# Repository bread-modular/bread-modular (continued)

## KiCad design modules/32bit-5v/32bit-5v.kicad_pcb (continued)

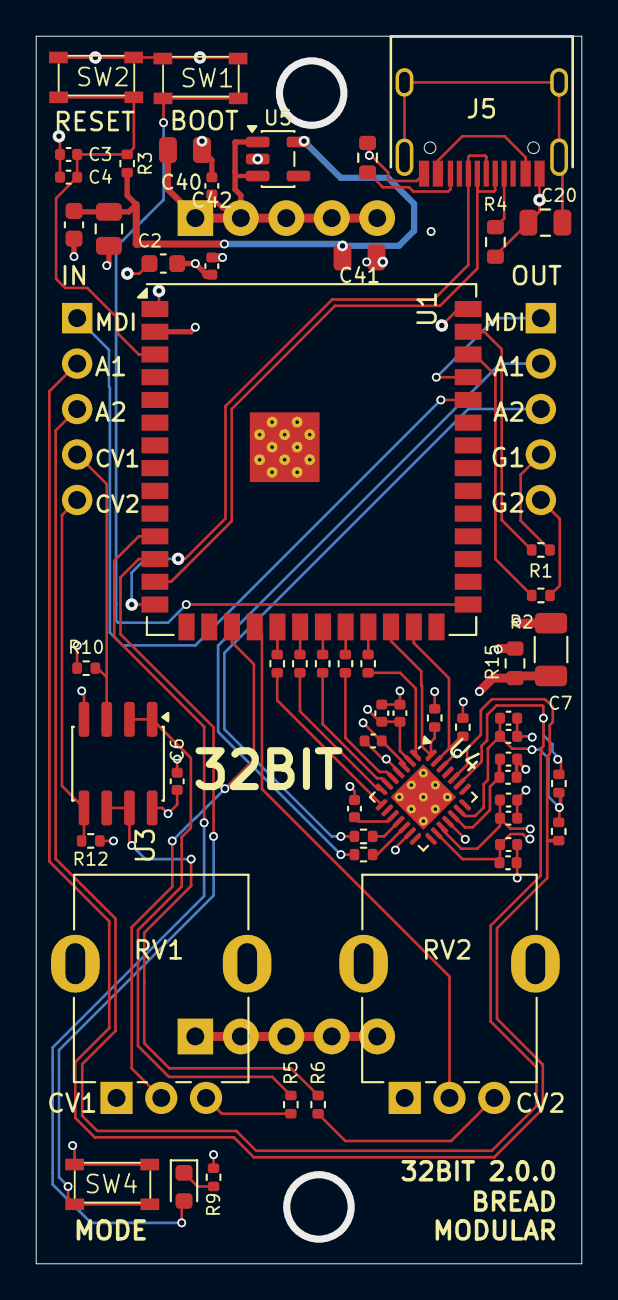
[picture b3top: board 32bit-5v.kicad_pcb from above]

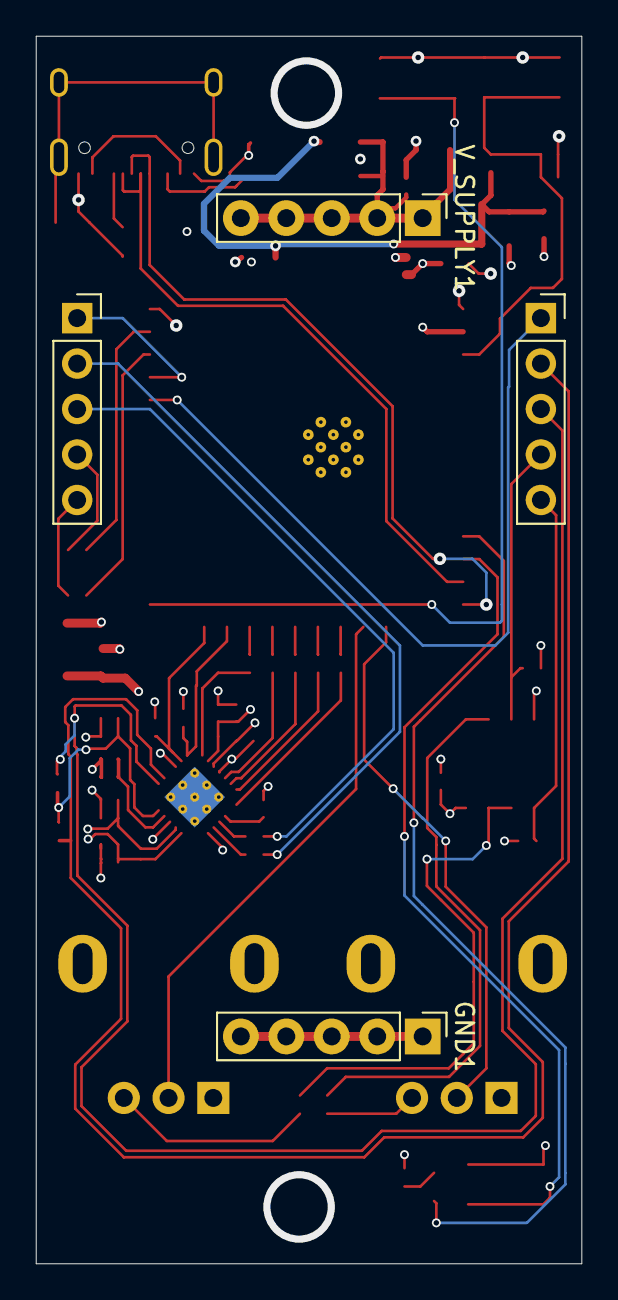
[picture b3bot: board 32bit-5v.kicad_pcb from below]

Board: 4 copper layers, 30.5 x 68.6 mm, 61 parts (4 on the bottom side), 51 nets.

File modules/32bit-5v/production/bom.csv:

Designator,Footprint,Quantity,Value,LCSC Part #
"C1,C4,C6,C21,C22,C26,C34,C36,C39",0402,9,0.1uf,
"C2,C8",0603,2,10uf,
C3,0402,1,1uf,
"C5,C27,C33,C35,C37,C38",0402,6,10uf,
"C7,C9,C10,C11,C12,C13",1206,6,100uf,
C20,0805,1,10nf,
C40,0805,1,10uf,C15850
C41,0805,1,22uf,C45783
D1,LED_0603_1608Metric,1,LED,
FB1,0805,1,GZ2012D121TF,
"GND1,V_SUPPLY1",Power_Connector,2,Conn_01x05_Pin,
"INPUT1,OUTPUT1",PinSocket_1x05_P2.54mm_Vertical,2,Conn_01x05_Socket,
J5,HRO-TYPE-C-31-M-12,1,USB_C_Receptacle_USB2.0_14P,
"R1,R2,R9,R13,R17",0402,5,1k,
R3,0402,1,10k,
"R4,R11",0603,2,5.1k,
"R5,R6",0402,2,1.5k,
"R7,R8,R14,R18,R26",0402,5,33,
"R10,R12,R16,R19",0402,4,100k,
R15,0603,1,10,
"R24,R25",0402,2,4.7k,
"RV1,RV2",Potentiometer_RV09,2,50k,
"SW1,SW2,SW4",K2-1808SN-A4SW-01,3,K2-1808SN-A4SW-01,
U1,ESP32-S3-WROOM-1U,1,ESP32-S3-WROOM-1U-N16R8,
U3,SOIC-8-1EP_3.9x4.9mm_P1.27mm_EP2.29x3mm,1,MCP6002-xSN,
U4,QFN-28-1EP_4x4mm_P0.45mm_EP2.4x2.4mm_ThermalVias,1,~,
U5,SOT-223-3_TabPin2,1,AP7361C-33E-13,C500795

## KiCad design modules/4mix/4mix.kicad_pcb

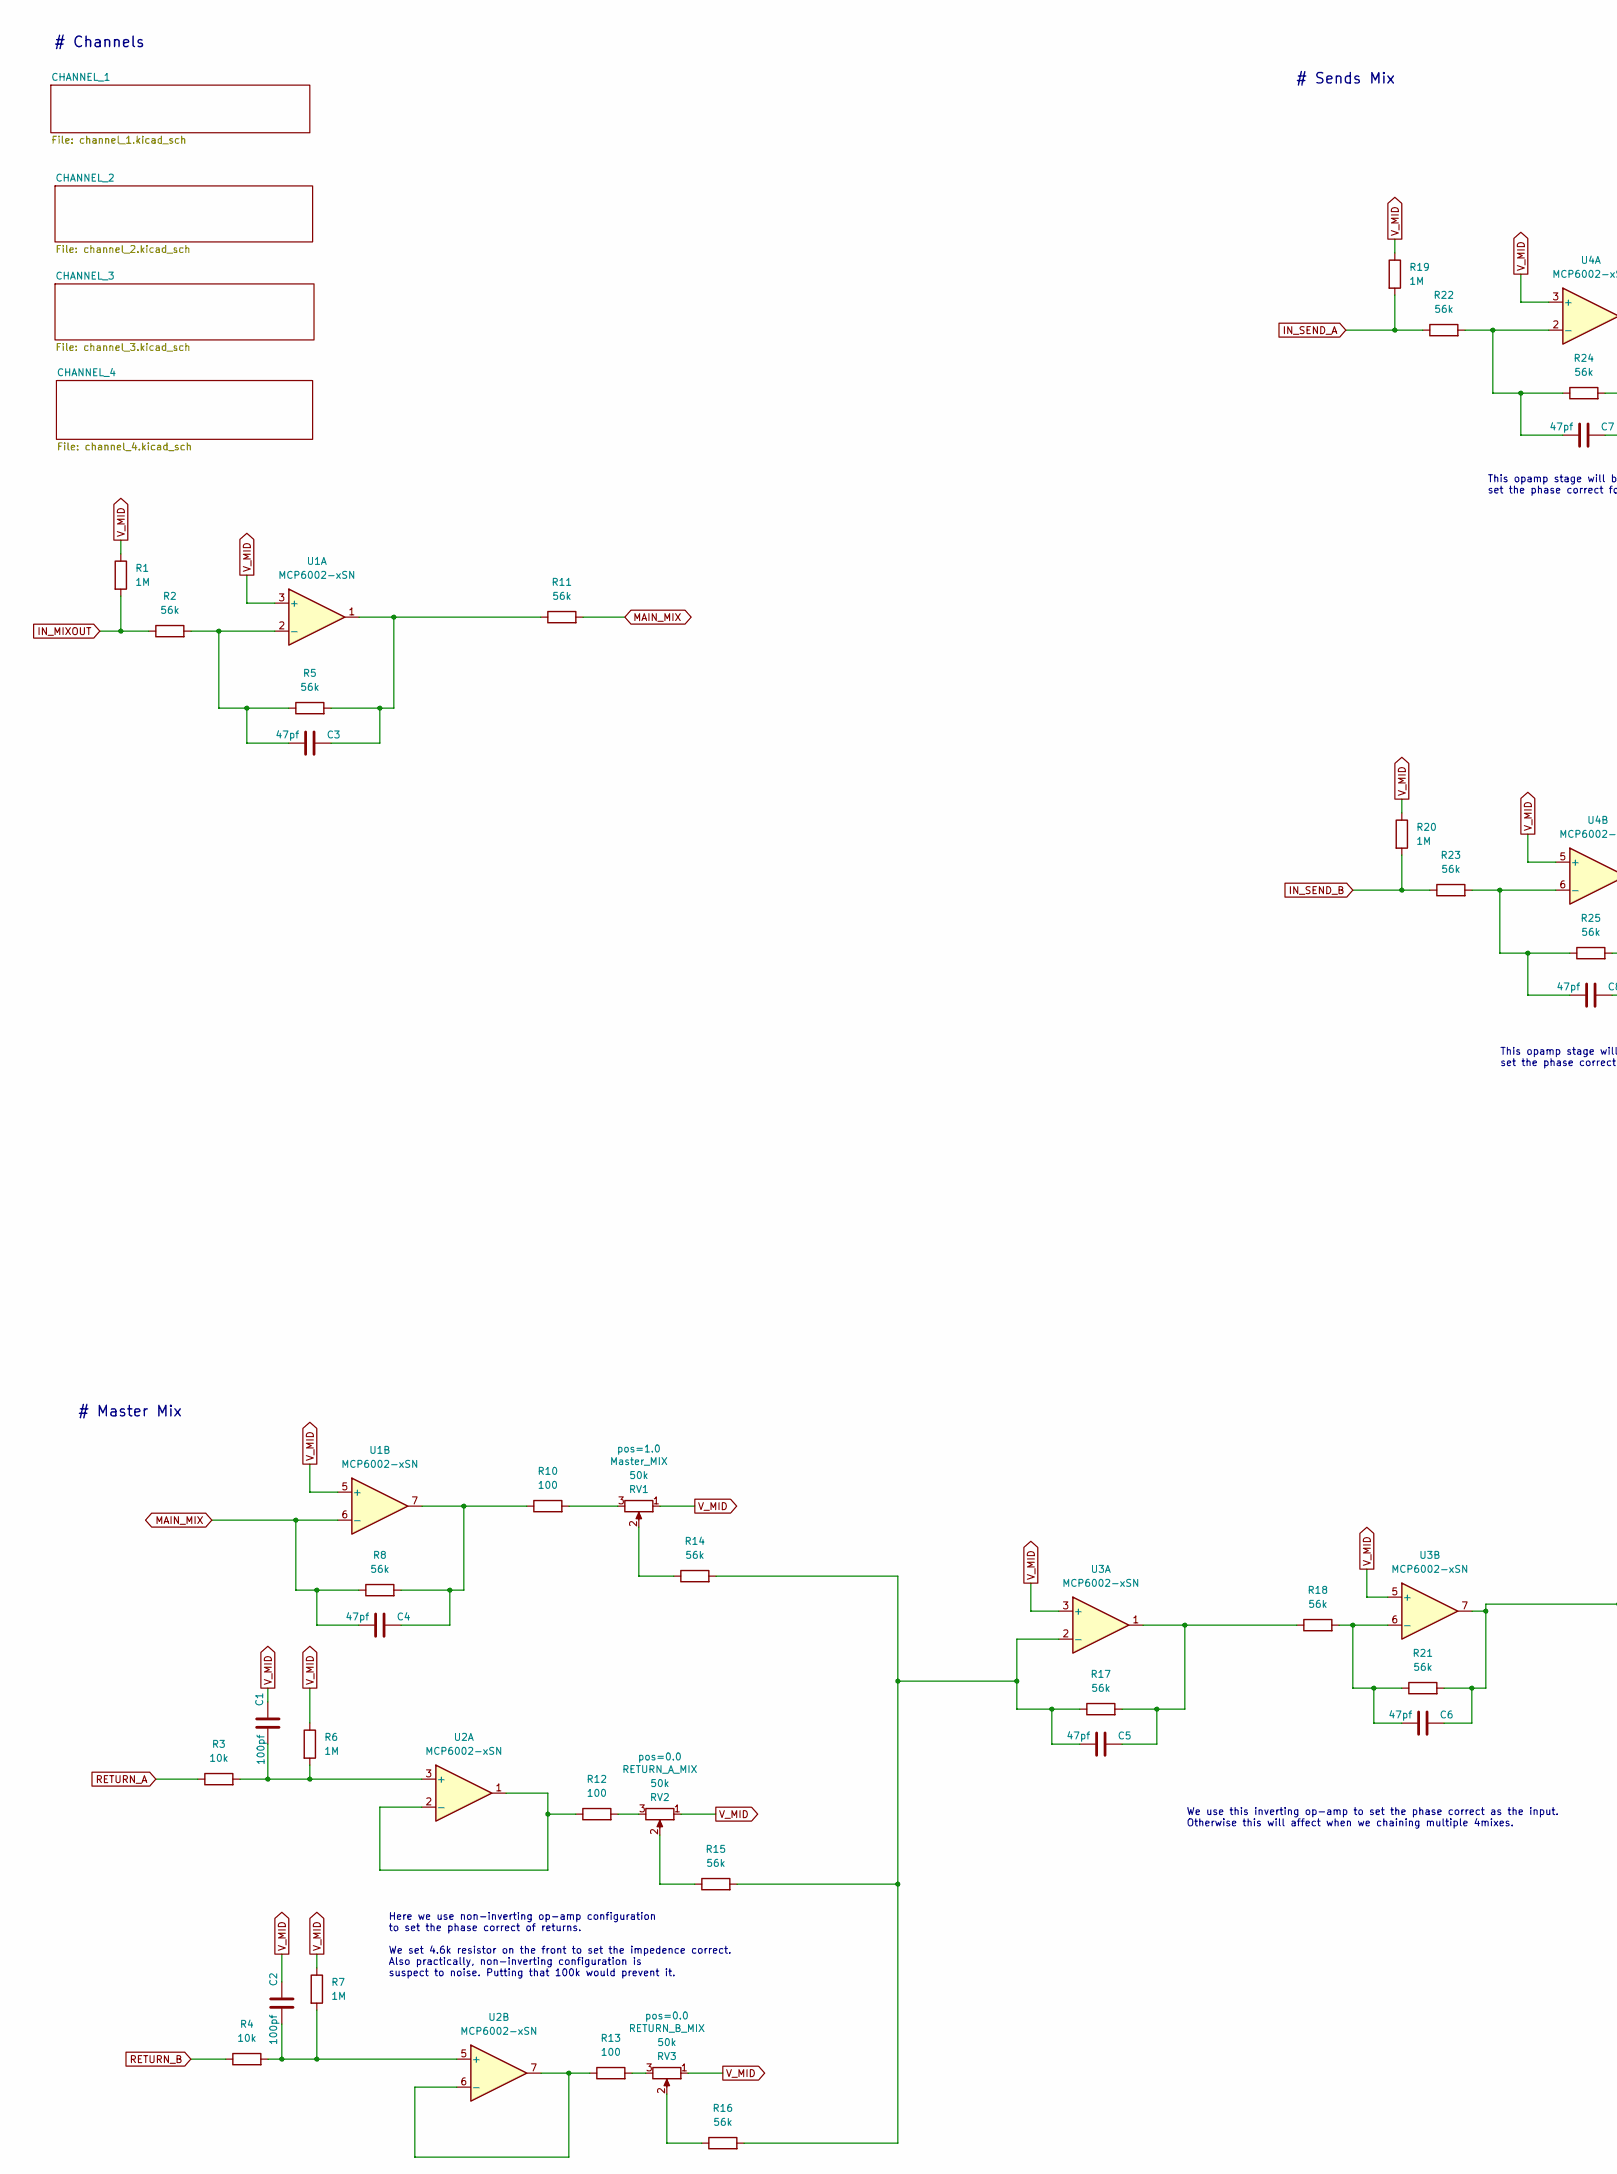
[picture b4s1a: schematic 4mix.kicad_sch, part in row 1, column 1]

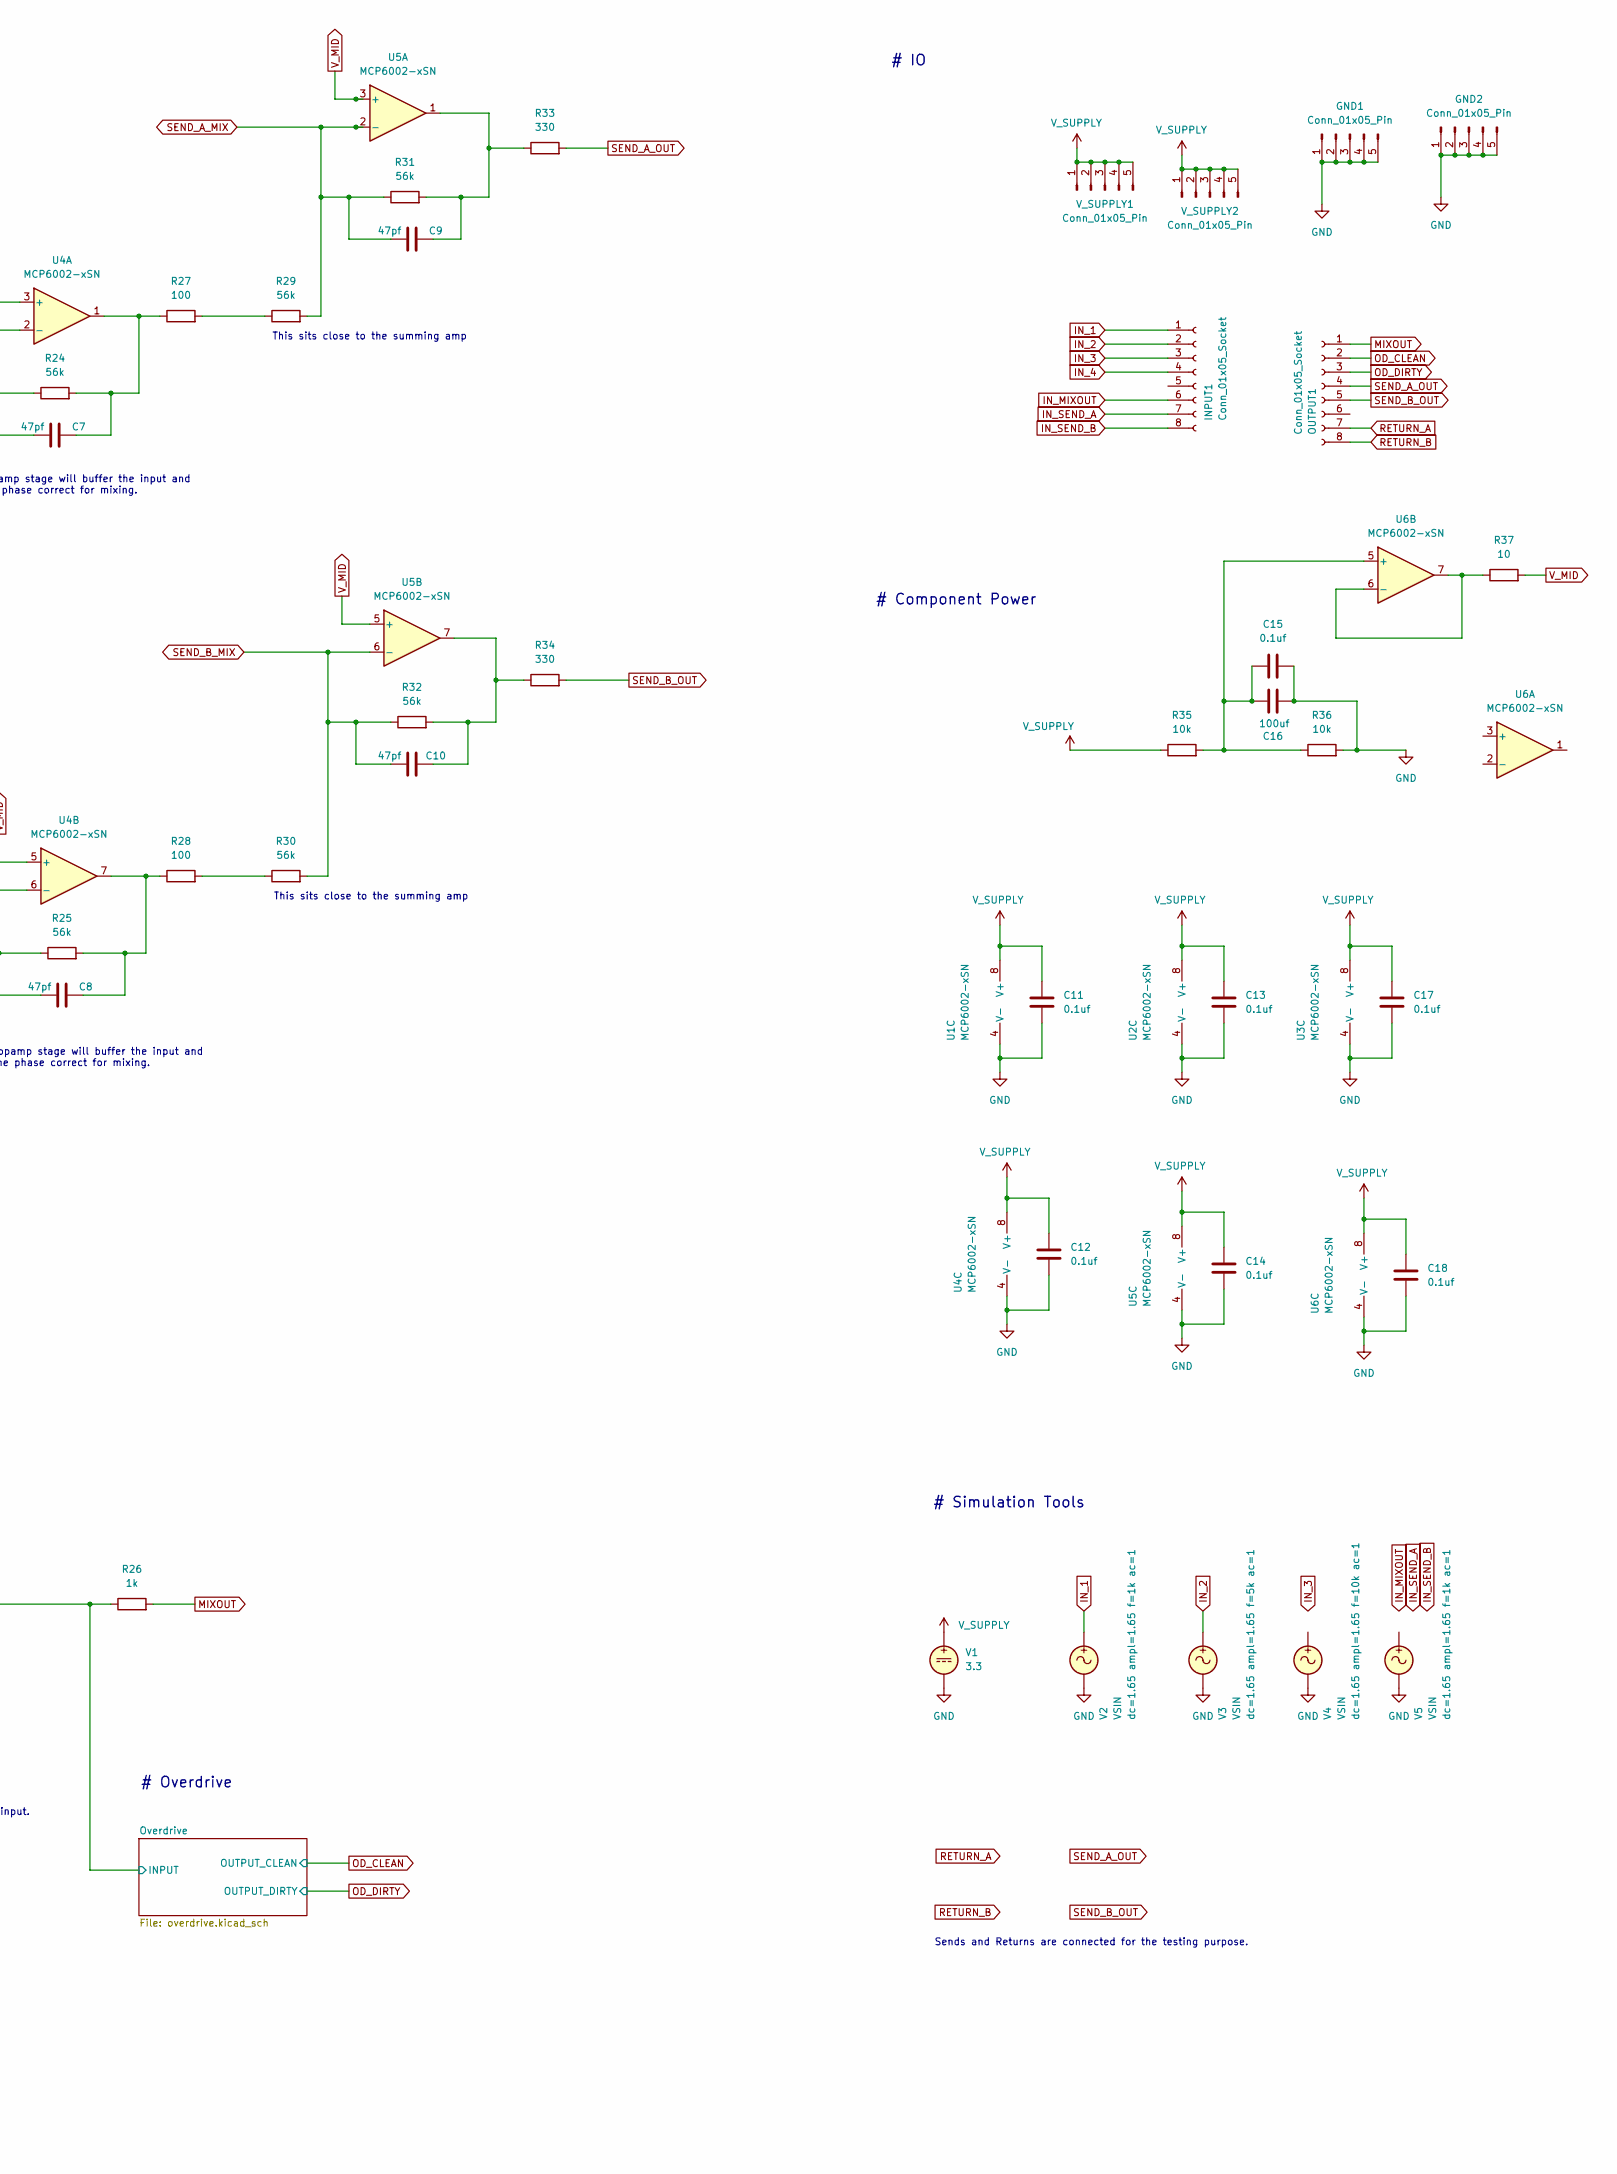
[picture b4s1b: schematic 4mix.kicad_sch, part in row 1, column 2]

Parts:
C1, C2: 100pf; C_0402_1005Metric
C3, C4, C5, C6, C7, C8, C9, C10: 47pf; C_0402_1005Metric
C11, C12, C13, C14, C15, C17, C18: 0.1uf; C_0402_1005Metric
C16: 100uf; C_1206_3216Metric
GND1, GND2: Conn_01x05_Pin; Power_Connector
INPUT1: Conn_01x05_Socket; PinSocket_1x08_P2.54mm_Vertical
OUTPUT1: Conn_01x05_Socket; PinSocket_1x08_P2.54mm_Vertical
R1, R6, R7, R19, R20: 1M; R_0402_1005Metric
R2, R5, R8, R11, R14, R15, R16, R17, R18, R21, R22, R23, R24, R25, R29, R30, R31, R32: 56k; R_0402_1005Metric
R3, R4, R35, R36: 10k; R_0402_1005Metric
R10, R12, R13, R27, R28: 100; R_0402_1005Metric
R26: 1k; R_0402_1005Metric
R33, R34: 330; R_0805_2012Metric
R37: 10; R_0402_1005Metric
RV1, RV2, RV3: 50k; Potentiometer_RV09
U1, U2, U3, U4, U5, U6: MCP6002-xSN; SOIC-8-1EP_3.9x4.9mm_P1.27mm_EP2.29x3mm
V1: 3.3
V2, V3, V4, V5: VSIN
V_SUPPLY1, V_SUPPLY2: Conn_01x05_Pin; Power_Connector

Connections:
/Overdrive/INPUT: C6.1, R21.2, R26.1, U3.7; also elsewhere on the board
GND: C11.2, C12.2, C13.2, C14.2, C15.2, C16.2, C17.2, C18.2, GND1.1, GND1.2, GND1.3, GND1.4, GND1.5, GND2.1, GND2.2, GND2.3, GND2.4, GND2.5, R36.2, U1.4 (V-), U2.4 (V-), U3.4 (V-), U4.4 (V-), U5.4 (V-), U6.4 (V-), V1.2, V2.2, V3.2, V4.2, V5.2; also elsewhere on the board
IN_1: INPUT1.1, V2.1; also elsewhere on the board
IN_2: INPUT1.2, V3.1; also elsewhere on the board
IN_3: INPUT1.3; also elsewhere on the board
IN_4: INPUT1.4; also elsewhere on the board
IN_MIXOUT: INPUT1.6, R1.2, R2.1
IN_SEND_A: INPUT1.7, R19.2, R22.1
IN_SEND_B: INPUT1.8, R20.2, R23.1
MAIN_MIX: C4.2, R8.1, R11.2, U1.6 (-); also elsewhere on the board
MIXOUT: OUTPUT1.1, R26.2
unnamed: C3.1, R5.2, R11.1, U1.1
unnamed: C4.1, R8.2, R10.1, U1.7
unnamed: C5.1, R17.2, R18.1, U3.1
unnamed: C7.1, R24.2, R27.1, U4.1
unnamed: C8.1, R25.2, R28.1, U4.7
unnamed: C9.1, R31.2, R33.1, U5.1
unnamed: C10.1, R32.2, R34.1, U5.7
unnamed: R10.2, RV1.3
unnamed: R12.2, RV2.3
unnamed: R13.2, RV3.3
unnamed: R14.1, RV1.2
unnamed: R15.1, RV2.2
unnamed: R16.1, RV3.2
unnamed: R27.2, R29.1
unnamed: R28.2, R30.1
unnamed: C3.2, R2.2, R5.1, U1.2 (-)
unnamed: C1.2, R3.2, R6.2, U2.3 (+)
unnamed: R12.1, U2.1, U2.2 (-)
unnamed: C2.2, R4.2, R7.2, U2.5 (+)
unnamed: R13.1, U2.6 (-), U2.7
unnamed: C5.2, R14.2, R15.2, R16.2, R17.1, U3.2 (-)
unnamed: C6.2, R18.2, R21.1, U3.6 (-)
unnamed: C7.2, R22.2, R24.1, U4.2 (-)
unnamed: C8.2, R23.2, R25.1, U4.6 (-)
unnamed: C15.1, C16.1, R35.2, R36.1, U6.5 (+)
unnamed: R37.1, U6.6 (-), U6.7
OD_CLEAN: OUTPUT1.2; also elsewhere on the board
OD_DIRTY: OUTPUT1.3; also elsewhere on the board
RETURN_A: OUTPUT1.7, R3.1
RETURN_B: OUTPUT1.8, R4.1
SEND_A_MIX: C9.2, R29.2, R31.1, U5.2 (-); also elsewhere on the board
SEND_A_OUT: OUTPUT1.4, R33.2
SEND_B_MIX: C10.2, R30.2, R32.1, U5.6 (-); also elsewhere on the board
SEND_B_OUT: OUTPUT1.5, R34.2
V_MID: C1.1, C2.1, R1.1, R6.1, R7.1, R19.1, R20.1, R37.2, RV1.1, RV2.1, RV3.1, U1.3 (+), U1.5 (+), U3.3 (+), U3.5 (+), U4.3 (+), U4.5 (+), U5.3 (+), U5.5 (+); also elsewhere on the board
V_SUPPLY: C11.1, C12.1, C13.1, C14.1, C17.1, C18.1, R35.1, U1.8 (V+), U2.8 (V+), U3.8 (V+), U4.8 (V+), U5.8 (V+), U6.8 (V+), V1.1, V_SUPPLY1.1, V_SUPPLY1.2, V_SUPPLY1.3, V_SUPPLY1.4, V_SUPPLY1.5, V_SUPPLY2.1, V_SUPPLY2.2, V_SUPPLY2.3, V_SUPPLY2.4, V_SUPPLY2.5; also elsewhere on the board

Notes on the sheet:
# Component Power
We use this inverting op-amp to set the phase correct as the input. Otherwise this will affect when we chaining multiple 4mixes.
# Simulation Tools
This sits close to the summing amp
# Channels
# Sends Mix
# Master Mix
This opamp stage will buffer the input and set the phase correct for mixing.
Here we use non-inverting op-amp configuration to set the phase correct of returns. We set 4.6k resistor on the front to set the impedence correct. Also practically, non-inverting configuration is suspect to noise. Putting that 100k would prevent it.
# Overdrive
Sends and Returns are connected for the testing purpose.
# IO

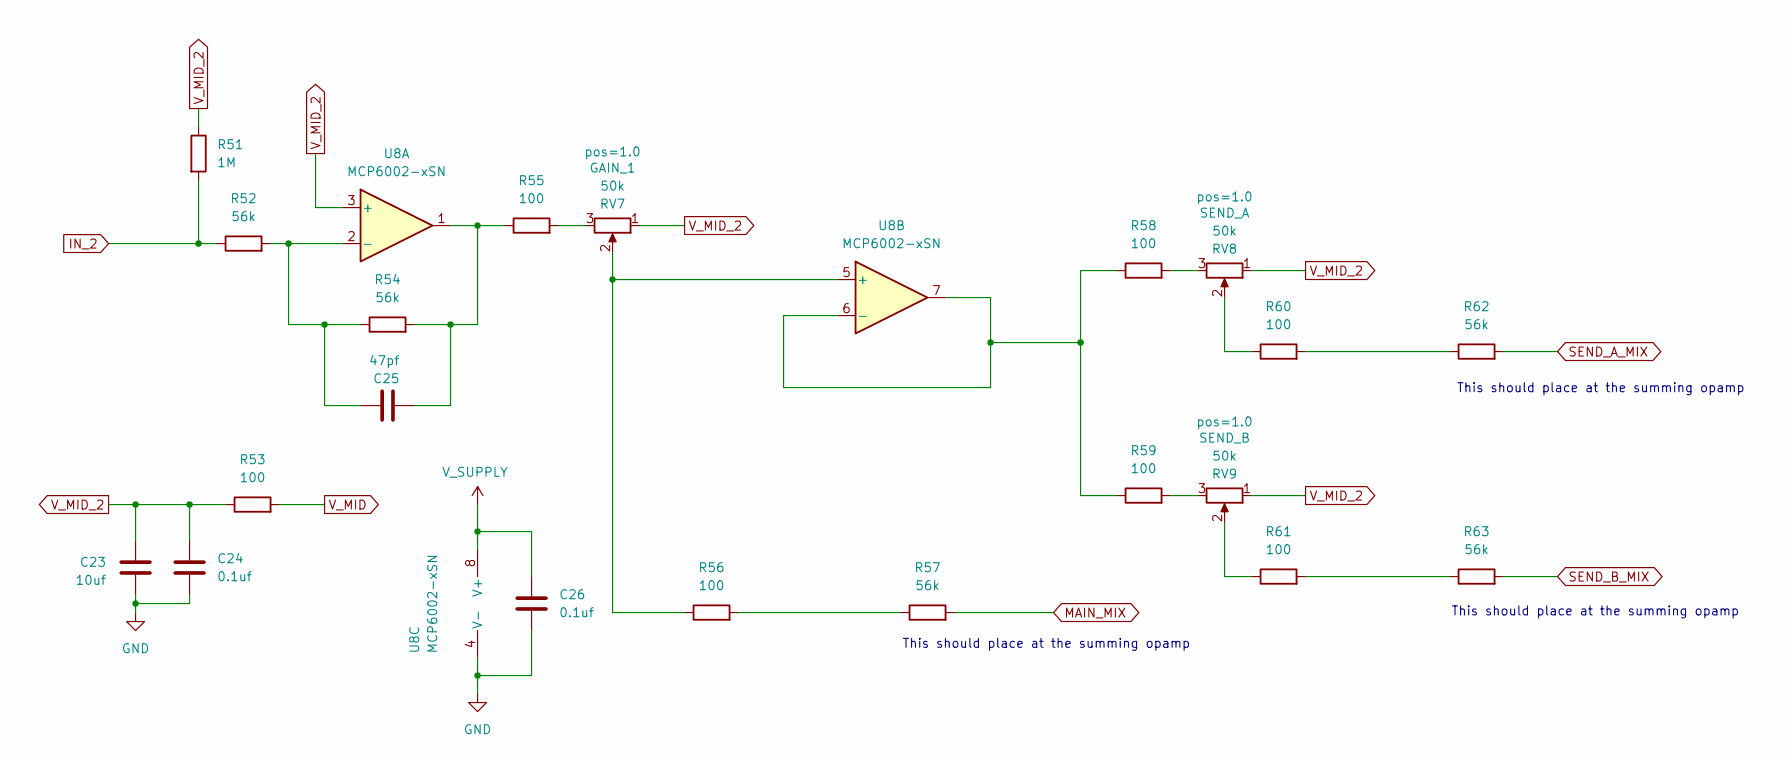
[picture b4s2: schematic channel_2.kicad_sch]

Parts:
C23: 10uf; C_0402_1005Metric
C24, C26: 0.1uf; C_0402_1005Metric
C25: 47pf; C_0402_1005Metric
R51: 1M; R_0402_1005Metric
R52, R54, R57, R62, R63: 56k; R_0402_1005Metric
R53, R55, R56, R58, R59, R60, R61: 100; R_0402_1005Metric
RV7, RV8, RV9: 50k; Potentiometer_RV09
U8: MCP6002-xSN; SOIC-8-1EP_3.9x4.9mm_P1.27mm_EP2.29x3mm

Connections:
GND: C23.2, C24.2, C26.2, U8.4 (V-); also elsewhere on the board
IN_2: R51.2, R52.1; also elsewhere on the board
MAIN_MIX: R57.2; also elsewhere on the board
unnamed: C25.2, R54.2, R55.1, U8.1
unnamed: R55.2, RV7.3
unnamed: R56.2, R57.1
unnamed: R58.2, RV8.3
unnamed: R59.2, RV9.3
unnamed: R60.1, RV8.2
unnamed: R60.2, R62.1
unnamed: R61.1, RV9.2
unnamed: R61.2, R63.1
unnamed: C25.1, R52.2, R54.1, U8.2 (-)
unnamed: R56.1, RV7.2, U8.5 (+)
unnamed: R58.1, R59.1, U8.6 (-), U8.7
SEND_A_MIX: R62.2; also elsewhere on the board
SEND_B_MIX: R63.2; also elsewhere on the board
V_MID: R53.2; also elsewhere on the board
V_MID_2: C23.1, C24.1, R51.1, R53.1, RV7.1, RV8.1, RV9.1, U8.3 (+)
V_SUPPLY: C26.1, U8.8 (V+); also elsewhere on the board

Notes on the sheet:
This should place at the summing opamp

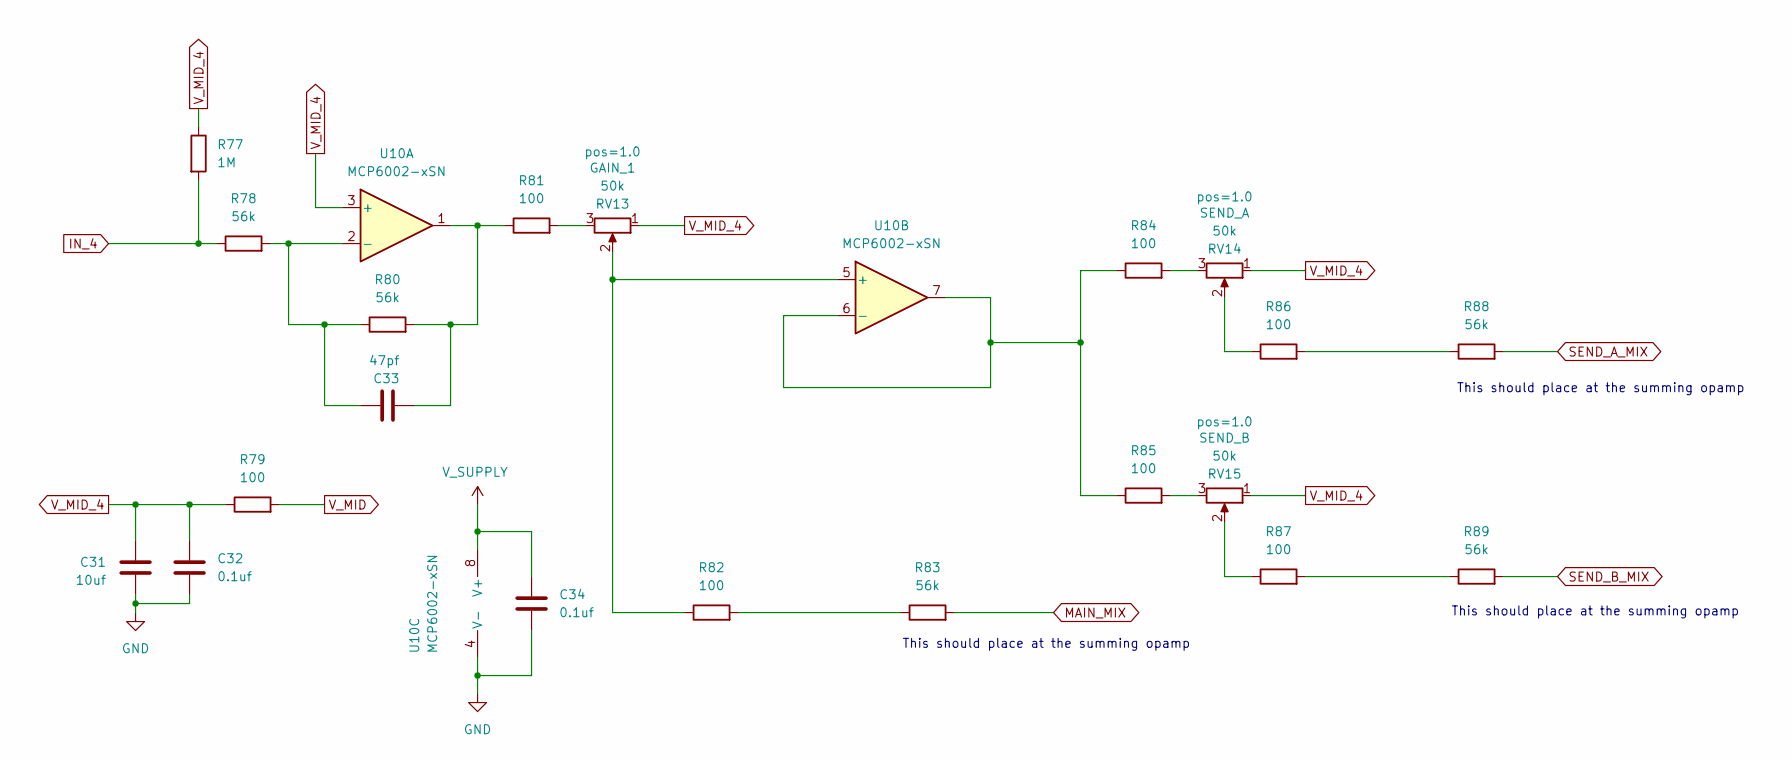
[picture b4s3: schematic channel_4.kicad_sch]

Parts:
C31: 10uf; C_0402_1005Metric
C32, C34: 0.1uf; C_0402_1005Metric
C33: 47pf; C_0402_1005Metric
R77: 1M; R_0402_1005Metric
R78, R80, R83, R88, R89: 56k; R_0402_1005Metric
R79, R81, R82, R84, R85, R86, R87: 100; R_0402_1005Metric
RV13, RV14, RV15: 50k; Potentiometer_RV09
U10: MCP6002-xSN; SOIC-8-1EP_3.9x4.9mm_P1.27mm_EP2.29x3mm

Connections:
GND: C31.2, C32.2, C34.2, U10.4 (V-); also elsewhere on the board
IN_4: R77.2, R78.1; also elsewhere on the board
MAIN_MIX: R83.2; also elsewhere on the board
unnamed: C33.2, R80.2, R81.1, U10.1
unnamed: R81.2, RV13.3
unnamed: R82.2, R83.1
unnamed: R84.2, RV14.3
unnamed: R85.2, RV15.3
unnamed: R86.1, RV14.2
unnamed: R86.2, R88.1
unnamed: R87.1, RV15.2
unnamed: R87.2, R89.1
unnamed: C33.1, R78.2, R80.1, U10.2 (-)
unnamed: R82.1, RV13.2, U10.5 (+)
unnamed: R84.1, R85.1, U10.6 (-), U10.7
SEND_A_MIX: R88.2; also elsewhere on the board
SEND_B_MIX: R89.2; also elsewhere on the board
V_MID: R79.2; also elsewhere on the board
V_MID_4: C31.1, C32.1, R77.1, R79.1, RV13.1, RV14.1, RV15.1, U10.3 (+)
V_SUPPLY: C34.1, U10.8 (V+); also elsewhere on the board

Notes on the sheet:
This should place at the summing opamp

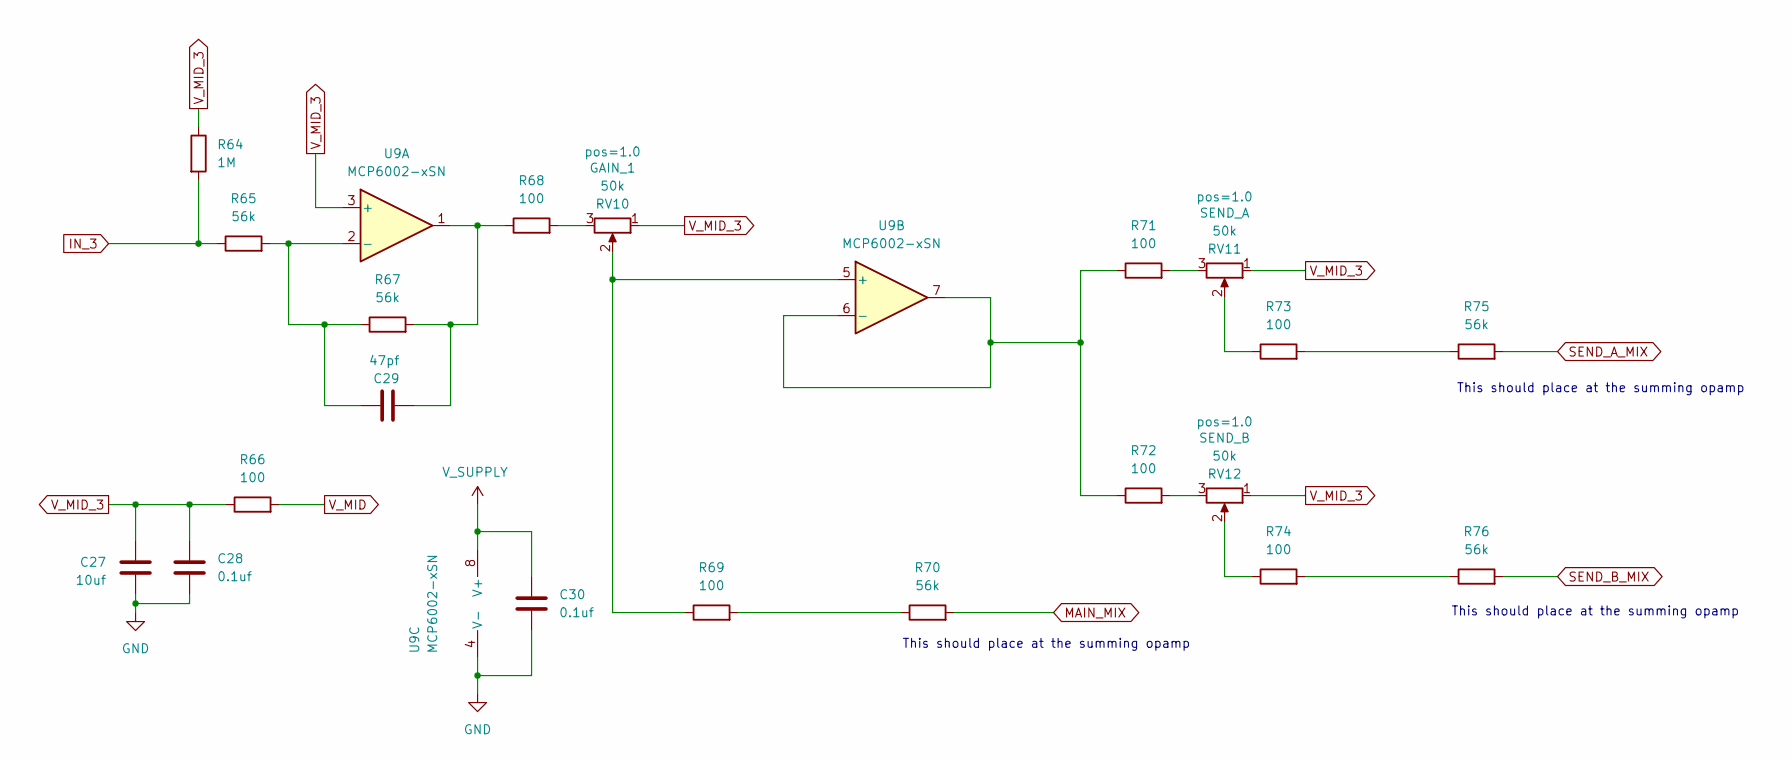
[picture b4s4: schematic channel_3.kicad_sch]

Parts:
C27: 10uf; C_0402_1005Metric
C28, C30: 0.1uf; C_0402_1005Metric
C29: 47pf; C_0402_1005Metric
R64: 1M; R_0402_1005Metric
R65, R67, R70, R75, R76: 56k; R_0402_1005Metric
R66, R68, R69, R71, R72, R73, R74: 100; R_0402_1005Metric
RV10, RV11, RV12: 50k; Potentiometer_RV09
U9: MCP6002-xSN; SOIC-8-1EP_3.9x4.9mm_P1.27mm_EP2.29x3mm

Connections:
GND: C27.2, C28.2, C30.2, U9.4 (V-); also elsewhere on the board
IN_3: R64.2, R65.1; also elsewhere on the board
MAIN_MIX: R70.2; also elsewhere on the board
unnamed: C29.2, R67.2, R68.1, U9.1
unnamed: R68.2, RV10.3
unnamed: R69.2, R70.1
unnamed: R71.2, RV11.3
unnamed: R72.2, RV12.3
unnamed: R73.1, RV11.2
unnamed: R73.2, R75.1
unnamed: R74.1, RV12.2
unnamed: R74.2, R76.1
unnamed: C29.1, R65.2, R67.1, U9.2 (-)
unnamed: R69.1, RV10.2, U9.5 (+)
unnamed: R71.1, R72.1, U9.6 (-), U9.7
SEND_A_MIX: R75.2; also elsewhere on the board
SEND_B_MIX: R76.2; also elsewhere on the board
V_MID: R66.2; also elsewhere on the board
V_MID_3: C27.1, C28.1, R64.1, R66.1, RV10.1, RV11.1, RV12.1, U9.3 (+)
V_SUPPLY: C30.1, U9.8 (V+); also elsewhere on the board

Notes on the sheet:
This should place at the summing opamp

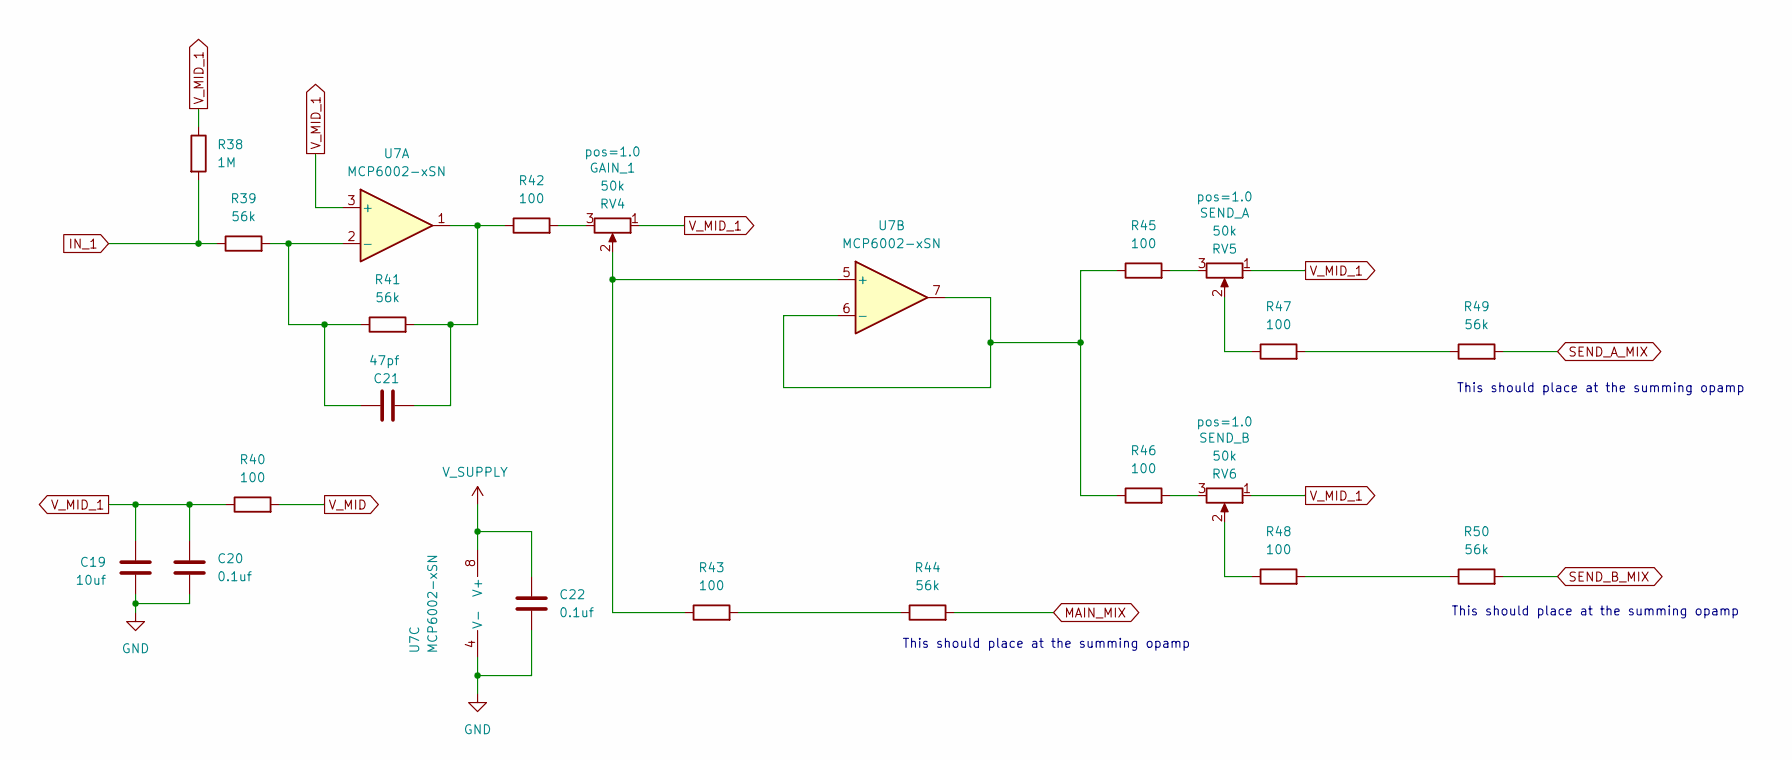
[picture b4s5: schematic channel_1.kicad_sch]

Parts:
C19: 10uf; C_0402_1005Metric
C20, C22: 0.1uf; C_0402_1005Metric
C21: 47pf; C_0402_1005Metric
R38: 1M; R_0402_1005Metric
R39, R41, R44, R49, R50: 56k; R_0402_1005Metric
R40, R42, R43, R45, R46, R47, R48: 100; R_0402_1005Metric
RV4, RV5, RV6: 50k; Potentiometer_RV09
U7: MCP6002-xSN; SOIC-8-1EP_3.9x4.9mm_P1.27mm_EP2.29x3mm

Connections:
GND: C19.2, C20.2, C22.2, U7.4 (V-); also elsewhere on the board
IN_1: R38.2, R39.1; also elsewhere on the board
MAIN_MIX: R44.2; also elsewhere on the board
unnamed: C21.2, R41.2, R42.1, U7.1
unnamed: R42.2, RV4.3
unnamed: R43.2, R44.1
unnamed: R45.2, RV5.3
unnamed: R46.2, RV6.3
unnamed: R47.1, RV5.2
unnamed: R47.2, R49.1
unnamed: R48.1, RV6.2
unnamed: R48.2, R50.1
unnamed: C21.1, R39.2, R41.1, U7.2 (-)
unnamed: R43.1, RV4.2, U7.5 (+)
unnamed: R45.1, R46.1, U7.6 (-), U7.7
SEND_A_MIX: R49.2; also elsewhere on the board
SEND_B_MIX: R50.2; also elsewhere on the board
V_MID: R40.2; also elsewhere on the board
V_MID_1: C19.1, C20.1, R38.1, R40.1, RV4.1, RV5.1, RV6.1, U7.3 (+)
V_SUPPLY: C22.1, U7.8 (V+); also elsewhere on the board

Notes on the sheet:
This should place at the summing opamp

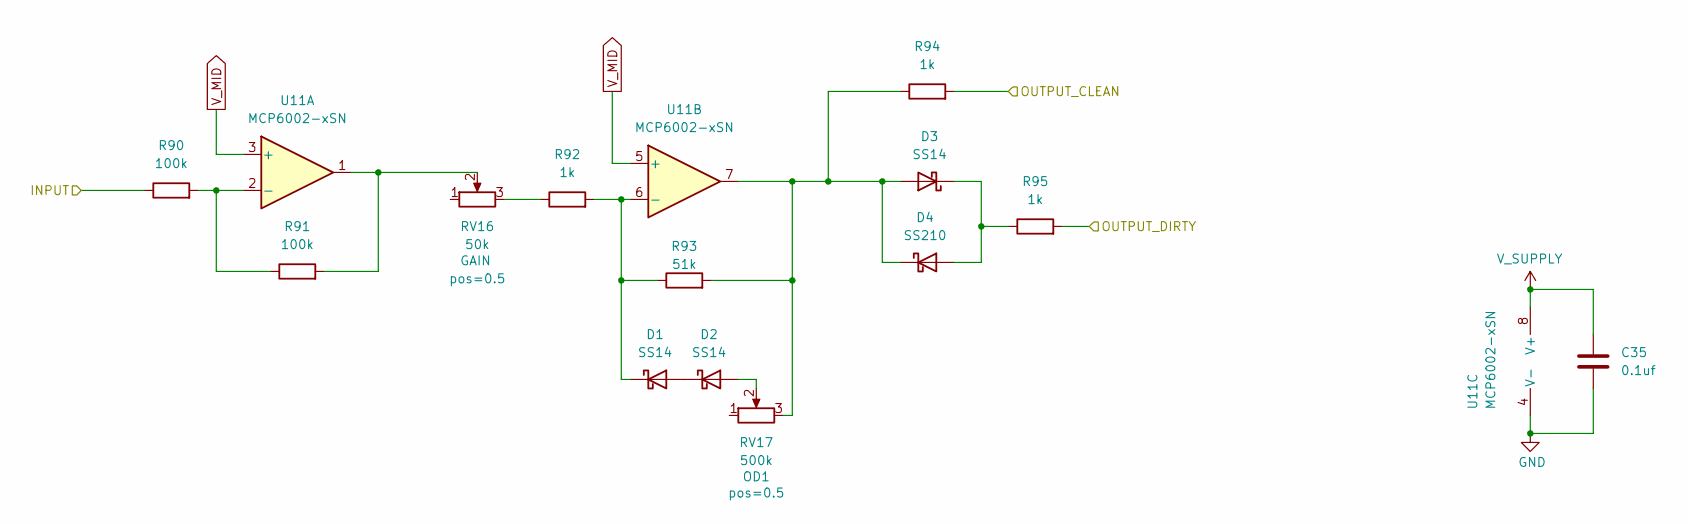
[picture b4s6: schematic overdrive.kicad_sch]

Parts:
C35: 0.1uf; C_0402_1005Metric
D1, D2, D3: SS14; D_SMA
D4: SS210; D_SMA
R90, R91: 100k; R_0402_1005Metric
R92, R94, R95: 1k; R_0402_1005Metric
R93: 51k; R_0402_1005Metric
RV16: 50k; Potentiometer_RV09
RV17: 500k; Potentiometer_RV09
U11: MCP6002-xSN; SOIC-8-1EP_3.9x4.9mm_P1.27mm_EP2.29x3mm

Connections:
/Overdrive/INPUT: R90.1; also elsewhere on the board
GND: C35.2, U11.4 (V-); also elsewhere on the board
unnamed: D1.2 (A), D2.1 (K)
unnamed: D1.1 (K), R92.2, R93.1, U11.6 (-)
unnamed: D2.2 (A), RV17.2
unnamed: D3.2 (A), D4.1 (K), R93.2, R94.1, RV17.3, U11.7
unnamed: D3.1 (K), D4.2 (A), R95.1
unnamed: R91.2, RV16.2, U11.1
unnamed: R92.1, RV16.3
unnamed: R90.2, R91.1, U11.2 (-)
OD_CLEAN: R94.2; also elsewhere on the board
OD_DIRTY: R95.2; also elsewhere on the board
V_MID: U11.3 (+), U11.5 (+); also elsewhere on the board
V_SUPPLY: C35.1, U11.8 (V+); also elsewhere on the board
